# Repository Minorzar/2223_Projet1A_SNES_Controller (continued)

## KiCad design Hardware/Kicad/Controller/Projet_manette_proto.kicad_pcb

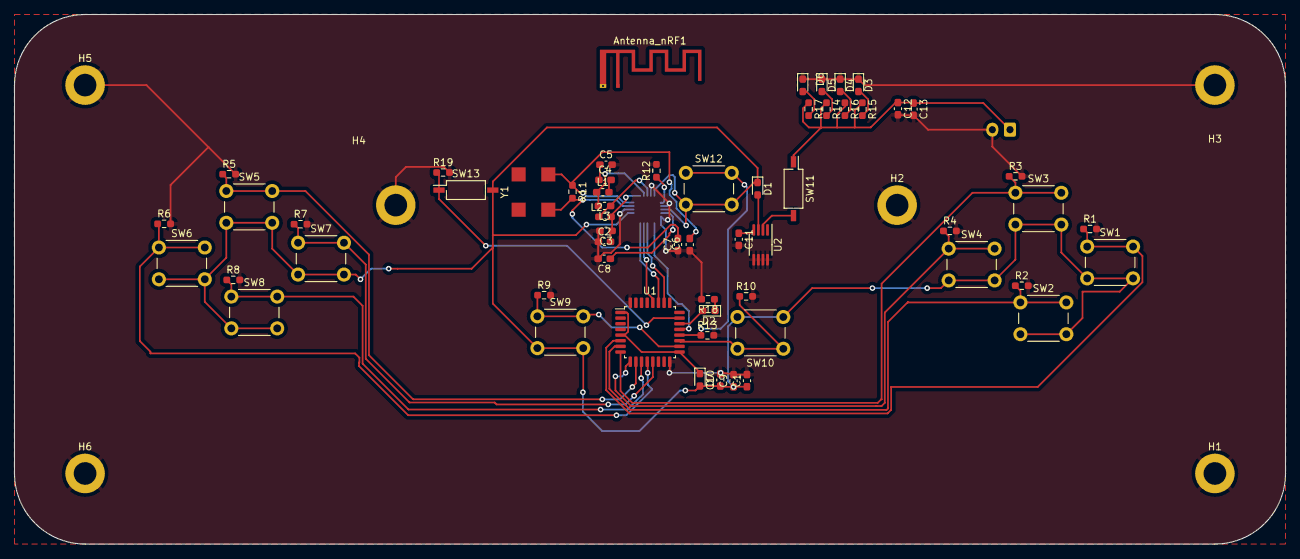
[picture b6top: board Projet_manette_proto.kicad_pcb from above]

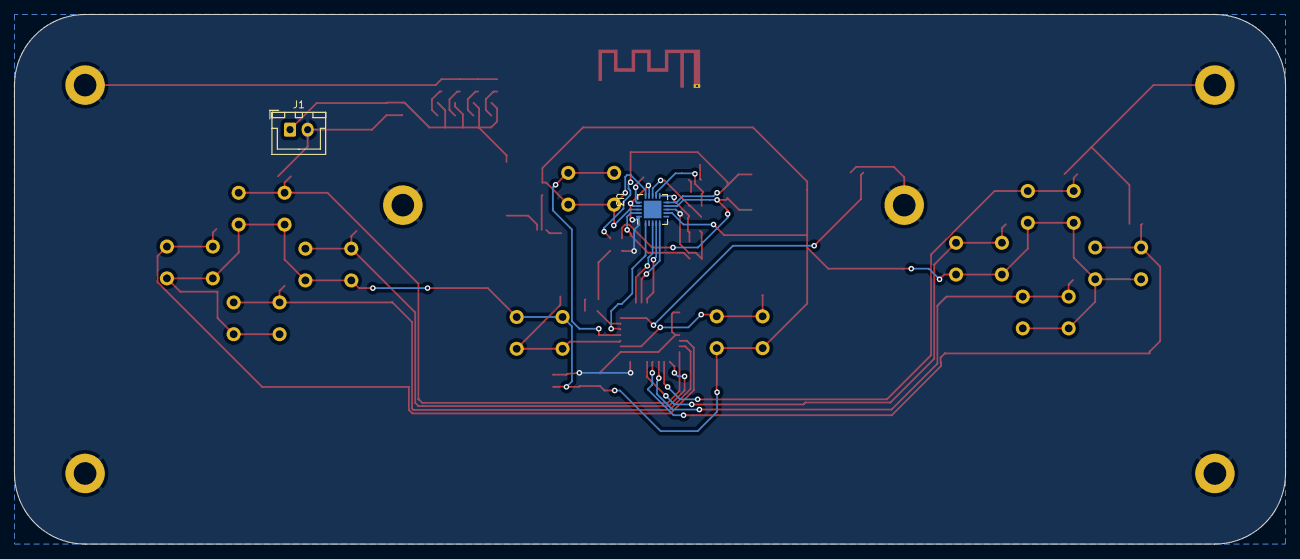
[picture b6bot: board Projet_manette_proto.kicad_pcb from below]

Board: 2 copper layers, 180.0 x 75.0 mm, 67 parts (2 on the bottom side), 38 nets.

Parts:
Antenna_nRF1: Texas_SWRA117D_2.4GHz_Right
C1: 100nF; C_0603_1608Metric_Pad1.08x0.95mm_HandSolder
C2: 4.7nF; C_0603_1608Metric_Pad1.08x0.95mm_HandSolder
C3: 2.2nF; C_0603_1608Metric_Pad1.08x0.95mm_HandSolder
C4: 1.5nF; C_0603_1608Metric_Pad1.08x0.95mm_HandSolder
C5: 1.0nF; C_0603_1608Metric_Pad1.08x0.95mm_HandSolder
C6, C7: 22nF; C_0603_1608Metric_Pad1.08x0.95mm_HandSolder
C8: 33nF; C_0603_1608Metric_Pad1.08x0.95mm_HandSolder
C9, C12: 1nF; C_0603_1608Metric_Pad1.08x0.95mm_HandSolder
C10: 10nF; C_0603_1608Metric_Pad1.08x0.95mm_HandSolder
C11: C_Small; C_0603_1608Metric_Pad1.08x0.95mm_HandSolder
C13: 1u; C_0603_1608Metric_Pad1.08x0.95mm_HandSolder
D1: LED_Small; LED_0603_1608Metric_Pad1.05x0.95mm_HandSolder
D2, D3, D4, D5, D6: LED; LED_0603_1608Metric_Pad1.05x0.95mm_HandSolder
D7: D_Small; D_0603_1608Metric_Pad1.05x0.95mm_HandSolder
H1, H2, H3, H4, H5, H6: MountingHole_Pad; MountingHole_3.2mm_M3_DIN965_Pad
J1: Conn_01x02; JST_XH_B2B-XH-A_1x02_P2.50mm_Vertical
L1: 3.9nH; L_0603_1608Metric_Pad1.05x0.95mm_HandSolder
L2: 2.7nF; L_0603_1608Metric_Pad1.05x0.95mm_HandSolder
L3: 8.2nF; L_0603_1608Metric_Pad1.05x0.95mm_HandSolder
R1, R2, R3, R4, R5, R6, R7, R8, R9, R10, R13, R18, R19: 1K; R_0603_1608Metric_Pad0.98x0.95mm_HandSolder
R11: 1M; R_0603_1608Metric_Pad0.98x0.95mm_HandSolder
R12: 22K; R_0603_1608Metric_Pad0.98x0.95mm_HandSolder
R14, R15, R16, R17: R_Small; R_0603_1608Metric_Pad0.98x0.95mm_HandSolder
SW1, SW2, SW3, SW4, SW5, SW6, SW7, SW8, SW9, SW10, SW12: SW_Push; SW_PUSH_6mm_H5mm
SW11, SW13: SW_DIP_x01; SW_DIP_SPSTx01_Slide_Copal_CHS-01B_W7.62mm_P1.27mm
U1: STM32L412KBTx; LQFP-32_7x7mm_P0.8mm
U2: MIC5219-3.3YMM; MSOP-8_3x3mm_P0.65mm
U3: NRF24L01; QFN-20-1EP_4x4mm_P0.5mm_EP2.5x2.5mm
Y1: 16MHz; Oscillator_SMD_EuroQuartz_XO91-4Pin_7.0x5.0mm

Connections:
A_Button: R1.1, SW1.1, U1.6 (PA0)
Antenna: Antenna_nRF1.1 (Feed_point), C4.1, C5.1
B_Button: R2.1, SW2.1, U1.7 (PA1)
DC_Button: R8.1, SW8.1, U1.11 (PA5)
Digital_Out_Put: U1.27 (PB4), U3.5 (MISO)
GND: Antenna_nRF1.2 (GND), C1.2, C2.1, C3.2, C5.2, C6.1, C7.1, C8.2, C9.2, C10.2, C11.2, C12.2, C13.2, D3.1 (K), D4.1 (K), D5.1 (K), D6.1 (K), H1.1, H2.1, H3.1, H4.1, H5.1, H6.1, J1.2, R1.2, R2.2, R3.2, R4.2, R5.2, R6.2, R7.2, R8.2, R9.2, R10.2, R12.2, R13.2, R18.2, R19.2, U1.16 (VSS), U1.32 (VSS), U2.5 (GND), U2.6 (GND), U2.7 (GND), U2.8 (GND), U3.8 (VSS), U3.14 (VSS), U3.17 (VSS), U3.20 (VSS)
Glob_Alim: C1.1, C9.1, C10.1, D1.1 (K), D7.2 (A), SW1.2, SW2.2, SW3.2, SW4.2, SW5.2, SW6.2, SW7.2, SW8.2, SW9.2, SW10.2, SW12.2, SW13.2, U3.7 (VDD), U3.15 (VDD), U3.18 (VDD)
LC_Button: R6.1, SW6.1, U1.12 (PA6)
LED_Order: D2.2 (A), U1.22 (PA12)
Li-ion: C12.1, C13.1, J1.1, R14.1, R15.1, R16.1, R17.1, SW11.1
MOSI: U1.28 (PB5), U3.4 (MOSI)
NES/SNES_switcher: R19.1, SW13.1, U1.23 (PA13)
unnamed: C4.2, L1.2
unnamed: D1.2 (A), U2.3 (OUT)
unnamed: D2.1 (K), R18.1
unnamed: D3.2 (A), R15.2
unnamed: D4.2 (A), R16.2
unnamed: D5.2 (A), R14.2
unnamed: D6.2 (A), R17.2
unnamed: D7.1 (K), U1.1 (VDD), U1.5 (VDDA), U1.17 (VDD)
unnamed: C11.1, U2.4 (BP)
unnamed: SW11.2, U2.2 (IN)
unnamed: L1.1, L3.2, U3.12 (ANT1)
unnamed: L2.1, L3.1, U3.13 (ANT2)
unnamed: C8.1, U3.19 (DVDD)
unnamed: R12.1, U3.16 (IREF)
unnamed: C6.2, R11.1, U3.10 (XC1), Y1.2
unnamed: C7.2, R11.2, U3.9 (XC2), Y1.1
Order_Search: R13.1, SW12.1, U1.20 (PA10)
Pin_Clock: U1.26 (PB3), U3.3 (SCK)
RC_Button: R7.1, SW7.1, U1.13 (PA7)
RX/TX: U1.21 (PA11), U3.1 (CE)
Return_ANT: C2.2, C3.1, L2.2, U3.11 (VDD_PA)
SE_Button: R10.1, SW10.1, U1.19 (PA9)
ST_Button: R9.1, SW9.1, U1.18 (PA8)
UC_Button: R5.1, SW5.1, U1.10 (PA4)
X_Button: R3.1, SW3.1, U1.8 (PA2)
Y_Button: R4.1, SW4.1, U1.9 (PA3)

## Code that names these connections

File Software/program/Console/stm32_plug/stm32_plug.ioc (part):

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Mcu.Name=STM32L412KBTx
Mcu.Package=LQFP32
Mcu.UserName=STM32L412KBTx
PA13\ (JTMS/SWDIO).Mode=Serial_Wire
PA13\ (JTMS/SWDIO).Signal=SYS_JTMS-SWDIO
PA14\ (JTCK/SWCLK).Mode=Serial_Wire
PA14\ (JTCK/SWCLK).Signal=SYS_JTCK-SWCLK
PA15\ (JTDI).Signal=GPIO_Output
PA2.Mode=Asynchronous
PA2.Signal=USART2_TX
PA3.Mode=Asynchronous
PA3.Signal=USART2_RX
PA4.Signal=GPIO_Input
PA5.Mode=Full_Duplex_Master
PA5.Signal=SPI1_SCK
PA6.Mode=Full_Duplex_Master
PA6.Signal=SPI1_MISO
PA7.Mode=Full_Duplex_Master
PA7.Signal=SPI1_MOSI
PA8.Signal=GPIO_Output
PA9.Signal=GPIO_Output
PB3\ (JTDO/TRACESWO).GPIOParameters=GPIO_PuPd
PB3\ (JTDO/TRACESWO).GPIO_PuPd=GPIO_PULLUP
PB3\ (JTDO/TRACESWO).Signal=GPIO_Output
PB4\ (NJTRST).Signal=GPIO_Output
PB5.GPIOParameters=GPIO_PuPd
PB5.GPIO_PuPd=GPIO_PULLUP
PB5.Signal=GPIO_Output
PB6.GPIOParameters=GPIO_PuPd
PB6.GPIO_PuPd=GPIO_PULLUP
PB6.Signal=GPIO_Output
PB7.GPIOParameters=GPIO_PuPd
PB7.GPIO_PuPd=GPIO_PULLUP
PB7.Signal=GPIO_Output
RCC.HSE_VALUE=8000000
board=custom

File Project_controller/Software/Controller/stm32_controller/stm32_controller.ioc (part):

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Mcu.Name=STM32L412KBTx
Mcu.Package=LQFP32
Mcu.UserName=STM32L412KBTx
PA1.Signal=ADCx_IN6
PA10.Mode=I2C
PA10.Signal=I2C1_SDA
PA11.GPIOParameters=GPIO_PuPd
PA11.GPIO_PuPd=GPIO_PULLUP
PA11.Signal=GPIO_Output
PA13\ (JTMS/SWDIO).Mode=Serial_Wire
PA13\ (JTMS/SWDIO).Signal=SYS_JTMS-SWDIO
PA14\ (JTCK/SWCLK).Mode=Serial_Wire
PA14\ (JTCK/SWCLK).Signal=SYS_JTCK-SWCLK
PA15\ (JTDI).GPIOParameters=GPIO_PuPd
PA15\ (JTDI).GPIO_PuPd=GPIO_PULLUP
PA15\ (JTDI).Signal=GPIO_Output
PA2.Mode=Asynchronous
PA2.Signal=USART2_TX
PA3.Mode=Asynchronous
PA3.Signal=USART2_RX
PA5.Mode=Full_Duplex_Master
PA5.Signal=SPI1_SCK
PA6.Mode=Full_Duplex_Master
PA6.Signal=SPI1_MISO
PA7.Mode=Full_Duplex_Master
PA7.Signal=SPI1_MOSI
PA9.Mode=I2C
PA9.Signal=I2C1_SCL
PB3\ (JTDO/TRACESWO).GPIOParameters=GPIO_PuPd
PB3\ (JTDO/TRACESWO).GPIO_PuPd=GPIO_PULLUP
PB3\ (JTDO/TRACESWO).Signal=GPIO_Output
PB5.GPIOParameters=GPIO_PuPd
PB5.GPIO_PuPd=GPIO_PULLUP
PB5.Signal=GPIO_Output
RCC.HSE_VALUE=8000000
board=custom

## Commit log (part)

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2023-04-03 Update of the readme file: more specifications on the project has been add as well as the updates to come
2023-04-03 Add files via upload
    Documentation sur les signaux de la manette SNES
2023-04-03 Creation of the readme_software file: this file will contains all the informations about the software of our project.
2023-04-03 Correction of a typo in the readme file: diagramm -> diagram
2023-04-03 this will be the first version of the README_HARDWARE
2023-04-03 File nRF24L01_Datasheet : this file is the datasheet of the transceiver we will use.
2023-04-03 Deleting untitled.rtf that was added by mistake
2023-04-03 Add of the general diagram of the controller
2023-04-03 first set up of README_HARDWARE we the NRF are present a
2023-04-04 Creation of main.c, function.c, function.h
2023-04-04 Correction of a typo made in the README.
2023-04-04 some presition on the Hardware (battery/ DC/DC convertor)
2023-04-04 some presition on the Hardware (battery/ DC/DC convertor) WITH THE LINE THIS TIME
2023-04-05 New presions on the Ward (choice DC/CD)
2023-04-05 Addition of the plug part in the readme of the hardware
2023-04-07 add folders
2023-04-08 Updated and corrected typos in README, README_SOFTWARE, README_HARDWARE. Created a folder Reference inside Datasheets. Added a source text file, new references and images.
2023-04-11 Add folders controller and console inside Software\program: will contain the code for the controller/console side
2023-04-11 Same as before just with the Console folder
2023-04-11 deletion of useless functions file inside the program folder: Makefile, function.c, function.h and main.c
2023-04-11 clean the git
2023-04-11 Deletion of an useless folder due to duplicate files: Hardware\Datasheet
2023-04-11 Add a more recent datasheet
2023-04-11 add achi
2023-04-11 Update of the main.c from the console side
2023-04-11 New version of Antenna
2023-04-11 Creation of the test project of the controller on cubeIDE. It's using another microprocessor to test it but the program will be the same (with the pins modified if needed)
2023-04-11 Antenna Datashit
2023-04-11 it's very to late to upload a Datasheet's DC/DC regualtor
2023-04-13 Initial push for the NRF24L01 code inside a STM32 project
2023-04-15 Creation of the readme file for routing (forgot in the previous commit) will need to be move in the readme folder once there will be a rounting added: the routing folder won't appear if empty
2023-04-15 controler Kicad v.0
2023-04-15 Add the two kicad schematic/PCB layer of the controller receptor in the hardware file, and a README about it.
2023-04-15 Deletion of an useless folder: Routing (missunderstanding inside the group)
2023-04-15 Updated Schematic & PCB / Work in progress (Tracks & Netclasses)
2023-04-16 Updated Schematic & PCB
2023-04-16 Updated Schematic & PCB (Bug Fixes)
2023-04-16 Updated Schematic & PCB (New netclasses / Antenna still need to be connected)
2023-04-16 Updated Schematic & PCB (Netclass, Power Flag, Library, Antenna)
2023-04-16 Updated Schematic & PCB (Netclass, Power Flag, Library, Antenna) 2
2023-04-16 Correction on the PCB layer of the nRF24ext model
2023-04-16 Correction of the last commit
2023-04-16 Update of the readme and the architecture of the files
2023-04-16 controler Kicad V0.1
2023-04-16 Updated NRF24L01 (Exclude & Include) Kicad projects to revision 2.0
2023-04-17 nRF24 full module on Arduino
2023-04-17 controler without nRF 24 homemade
2023-04-17 libery correction
2023-04-17 CONTROLER V1
2023-04-17 Renamed files
2023-04-17 cristal datasheet found by seg
2023-04-17 L ET RRRRRRRRRRRRRRRRRRRRRR
2023-04-17 correction
2023-04-17 Sorted Hardware
2023-04-17 A new datasheet are coming git add ./!
2023-04-17 Corrective changes on the Plug_NRF24L01_Exclude KiCad
2023-04-17 Updated NRF24L01_Include
2023-04-17 Thanks M.Papazoglou,more led, more Software problem
2023-04-17 New vers Controler
2023-04-18 Updated Plug_NRF24L01_Include Schematic & Include (Added new components and modified footprints). Fixed some errors on NRF24L01_Exclude.
2023-04-18 Updated PCB (Grouping and Tracks)
2023-04-18 New controler versions, and not the last
2023-04-19 Updated Plug_NRF24L01_Include. Schematic (Pins assignment / Appairing Button). PCB (Finalized routing / Antenna not working).
2023-04-19 Updated Plug_NRF24L01_Include (Version 1.0) - Schematic (New pins assignment / New button / New SWD Connector) - PCB (Finalized Routing / Antenna not working)
2023-04-19 Fixed image (PLUG_NRF24L01_Include_V1_Schematic)
2023-04-19 Updated Plug_NRF24L01_Exclude (Version 1.0) - Schematic (New pins assignment / New buttons) - PCB (Completed Routing V1)
2023-04-23 New New controler vers
2023-04-27 Updated Plug_NRF24L01_Include (V1.1) - PCB
2023-04-27 Updated Plug_NRF24L01_Include (V1.1a) - Fixes (Text)
2023-04-28 Updated Plug_NRF24L01_Include (V1.1b) - Fixes (Keepout area)
2023-04-28 Updated Plug_NRF24L01 (Text, ruler, images)
2023-04-30 New New New version of the controler include, we hope that will be the last
2023-05-03 And a new version of the controler
2023-05-03 Maybe the final version
2023-05-03 Exculde Time
2023-05-03 Exculde finish
2023-05-03 New files
2023-05-04 Change the name of a folder that was missnamed
2023-05-04 new vers down
2023-05-04 new vers shell
2023-05-04 changed the flowcharts to display which processes will be defined outside of the main code (we will use a custom library)
2023-05-04 update of the folder 'controler_NRF24L01_Exclude' -> replace by the correction given
2023-05-04 updated the code for the controller. Added pin declarations and finished the process that gathers button data and puts it on 2 bytes
2023-05-09 Update PCB
2023-05-09 Change of the nRF24 connector on the PCB (1mm -> 2.54mm)
2023-05-09 test commit because something was broken for the other ones
2023-05-09 updated pinout in console and controller code, added comments showing where the WIP functions should be
2023-05-09 Updated Plug_NRF24L01_Exclude (V2.0) - Schematic (NRF24 Connector) - PCB (Capacitor)
2023-05-09 Added a capacitor of 10u for the power of the STM32 on the schematics of the plugs
2023-05-09 Updated Plug_NRF24L01_Exclude (V2.1) - Schematic & PCB (Added 10μ Capacitor)
2023-05-09 created a custom library for the nrf24 module. I've written a few functions in it: transmitting data, receiving data, writing in registers. Initialisation function is WIP.
2023-05-09 new shell
2023-05-09 finished the initialisation function, not sure if it works
2023-05-10 V.1 of the full shell controller
2023-05-11 V.15 shell
2023-05-12 Updated Plug_NRF24L01_Include (V2.1) - Schematic & PCB & Image
2023-05-12 Update Plug_NRF24L01_Exclude (V2.1b) - Schematic & Image (Bug Fix)
2023-05-15 V.152 shell
2023-05-15 added separate init protocols for the plug and the controller, though they are the same for now. Added extra comments. Delays still to be defined.
2023-05-15 nrf24 module is now always in RX/TX mode during operation, module switches to this mode in the initialization. Fixed var name 'register' being a data type.
2023-05-15 Base code for the controller, contains the test for the UART transmission and the library for the NR24
2023-05-15 Correction in the code, add of a LED test to see if it's working (only the UART is working currently, SPI not yet implemented)
2023-05-15 Correction of the correction
2023-05-15 added CSN enabling at each command start and disabling at each end. Added new command nrf24_R_REGISTER for debug purposes
2023-05-16 V.2 shell
2023-05-16 added a datasheet for the LED bus, added a function in the nrf24 library for debug purposes
2023-05-16 Add a library for NRF24 inside the projet, currently the library only handel Transmit and seems to be have an unknown issue somewhere. Still working on it
2023-05-16 Very small correction in the library, CS pin is not supposed to be modified inside the init function. The error is still not found but is inside the init (maybe an error in the adresses or inside the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
2023-05-16 Kicad fixed
2023-05-16 begin shell plug
2023-05-16 Correction of one of the error the code add. Now the transmission seems to work but there is a problem with the receive: the FIFO is always empy and no data can be collected from it (so maybe the tra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
2023-05-17 Newer version of the library, add a function that allows to see the content of all the register inside the NRF24. Transmit seems to work fine now, still working on the receive
2023-05-21 V-1.5 controler
2023-05-22 Updated Plug_NRF24L01_Exclude (Ground vias)
2023-05-22 Update v2.2a - Plug_NRF24L01_Exclude (SWD_Connector, GND Vias) - Controller_NRF24L01_Exclude (Schematic) - Cleaned Folders
2023-05-22 V.2 controler
2023-05-22 more datasheet
2023-05-22 Update Plug_NRF24L01 v3.0a (Warnings remaining only)
2023-05-22 V.2.2 shell controler
2023-05-22 Upadte Plug_NRF24L01_Exclude v3.0b (Completed routing / Added images)
2023-05-23 Update Plug_NRF24L01_Exclude v3.0b (Minor changes)
2023-05-23 Update Plug_NRF24L01_Exclude v3.0c (Minor routing changes / New images)
2023-05-23 Update Plug_NRF24L01_Exclude v3.0c (Commit fixes)
2023-05-23 Update Plug_NRF24L01_Exclude v3.0d (Minor silkscreen changes)
2023-05-23 Update Plug_NRF24L01_Exclude v3.0d (Updated images)
2023-05-23 change size vias
2023-05-23 V.2.3
2023-05-24 V.2.4
2023-05-24 shell V.3
2023-05-28 Controler V.3
2023-05-28 final version
2023-05-30 fix pcb v3
2023-05-30 added the (almost) completed stm32 projects. The only part missing is the wireless communication
2023-05-30 Update Plug_NRF24L01_Exclude V1-2-3-4 / Readme_Hardware
2023-05-30 more information on the README_KICAD
2023-05-30 Update Plug_NRF24L01_Exclude v4.0a (Schematic Fixes / New PCB Routing) - Added new images
2023-06-01 add pcb v5 for plug
2023-06-02 updated pins and cleaned up the SOftware directory
2023-06-02 Update README_HARDWARE
2023-06-02 Updated README_HARDWARE - Cleaned Plug_NRF24L01 folders
2023-06-02 Updated README_KICAD (WIP)
2023-06-05 Final correction of the nrf24 library. It seems to be working know even so their must be a problem (I hope due to the cable)
2023-06-05 Update of the 3D model
2023-06-05 Add all readMe links on the main readMe
2023-06-05 Typo in the main readMe
2023-06-05 SEE YOU SHEEL COWBOY
2023-06-06 finished merging the different code files into 2 projects. Code should be entirely functional
2023-06-06 Update README, README_HARDWARE
2023-06-06 END OF TIME
2023-06-06 Comment the previous programm, also made it cleaner
2023-06-07 Update README_KICAD
2023-06-07 Update README_KICAD (Fixed & WIP)
2023-06-09 Update README_KICAD (Folder structure / Schematic)
2023-06-09 Update README_KICAD (Formatting Syntax Test)
2023-06-09 Update README_KICAD (Formatting Syntax Test 2)
2023-06-09 updated the readme related to software
2023-06-09 Update README_KICAD (Completed)
2023-06-09 Added a new link section on each readme. Minor changes to README and README_KICAD.
2023-06-09 Fixed README_SOFTWARE
2023-06-09 Update of readme files: soft -> correction of a statement, hard -> add the reason why we choose the nrf24
2023-06-09 Fixed README
2023-06-09 Updated README_SOFTWARE (WIP)
2023-06-09 Updated README_SOFTWARE (Final?)
2023-06-09 Updated README, README_HARDWARE, README_KICAD, README_SOFTWARE
2023-06-24 Update of the repository, prepare it for the second part of the project: the consol itsefl
2023-06-24 Update of the repository, prepare it for the second part of the project: the consol itself
2023-09-19 Add the folders to start working on the project. Create the FPGA project with DE1-SoC board. txt files were added so the folders would be seen by the other collaborators. Typos have been corrected.
2023-09-26 Added documents (65816 Primer, SNES Developer Manual Book 1 & 2)
2023-09-26 Replaced corrupted datasheets with text versions
